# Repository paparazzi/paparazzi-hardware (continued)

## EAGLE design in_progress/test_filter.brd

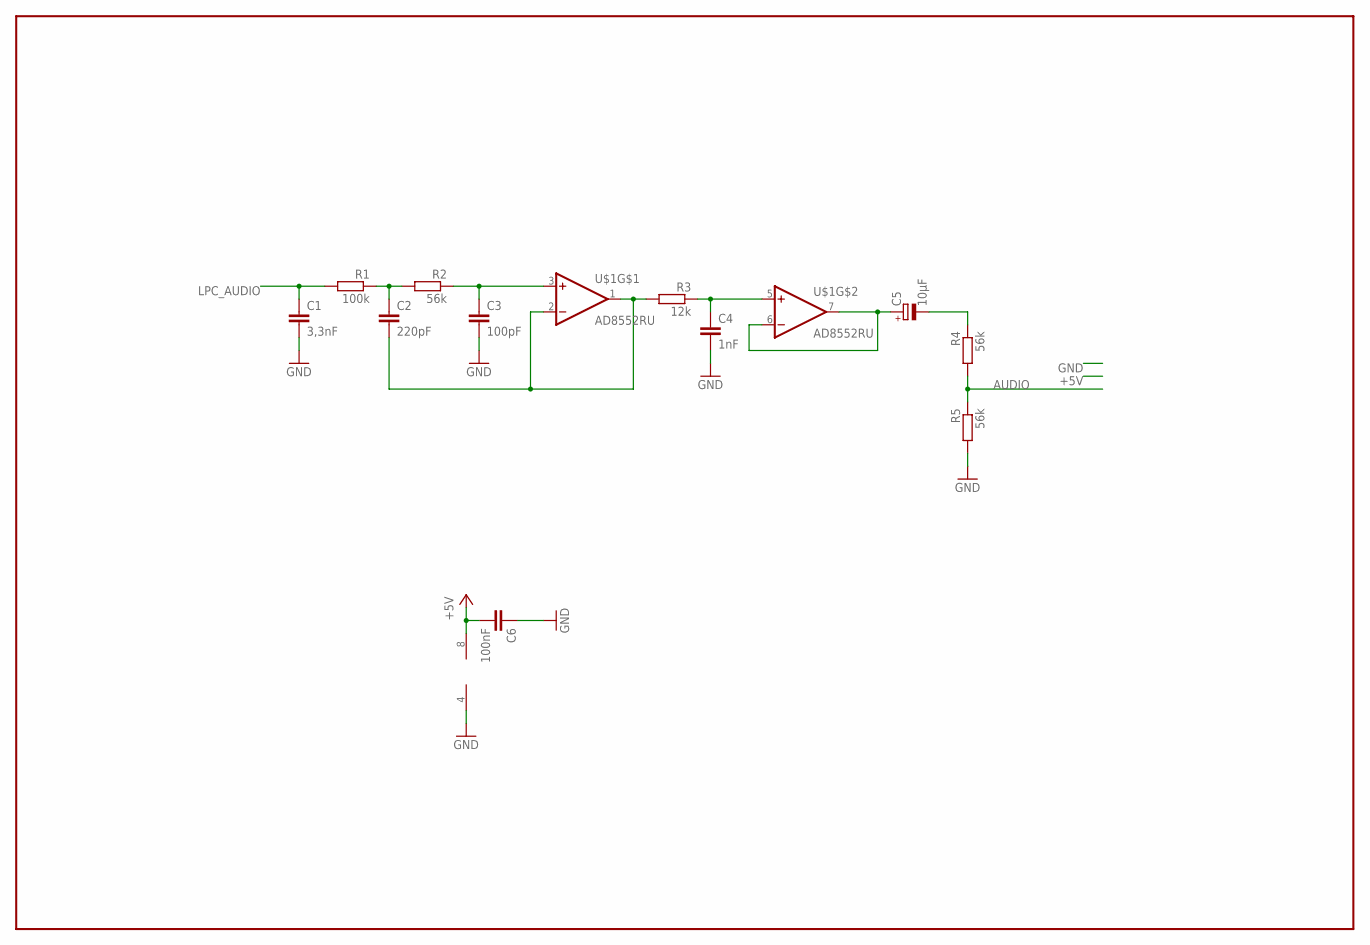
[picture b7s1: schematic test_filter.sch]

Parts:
C1: 3,3nF; C050-030X075
C2: 220pF; C050-030X075
C3: 100pF; C050-030X075
C4: 1nF; C050-030X075
C5: 10µF; E2,5-7
C6: 100nF; C050-030X075
R1: 100k; 0204/7
R2, R4, R5: 56k; 0204/7
R3: 12k; 0204/7
U$1: AD8552RU; TSSOP8

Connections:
+5V: C6.2, U$1.8 (V+)
AUDIO: R4.2, R5.1
GND: C1.2, C3.2, C4.2, C6.1, R5.2, U$1.4 (V-)
LPC_AUDIO: C1.1, R1.2
unnamed: C5.+, U$1.6 (-IN), U$1.7 (OUT)
unnamed: C2.2, R3.2, U$1.1 (OUT), U$1.2 (-IN)
unnamed: C2.1, R1.1, R2.2
unnamed: C3.1, R2.1, U$1.3 (+IN)
unnamed: C5.-, R4.1
unnamed: C4.1, R3.1, U$1.5 (+IN)

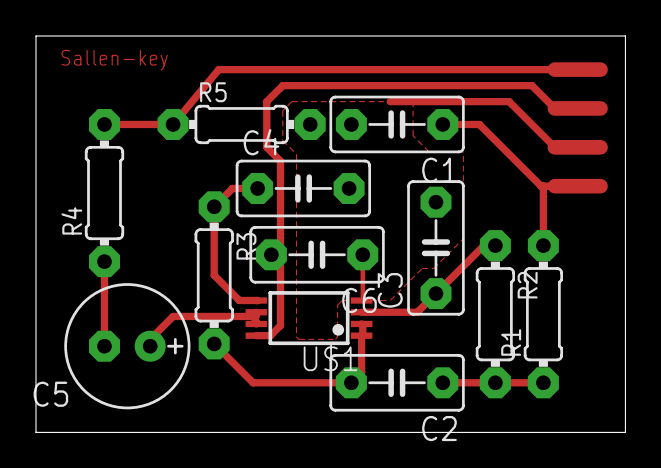
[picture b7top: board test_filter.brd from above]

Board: 2 copper layers, 32.7 x 22.0 mm, 12 parts (0 on the bottom side), 10 nets.

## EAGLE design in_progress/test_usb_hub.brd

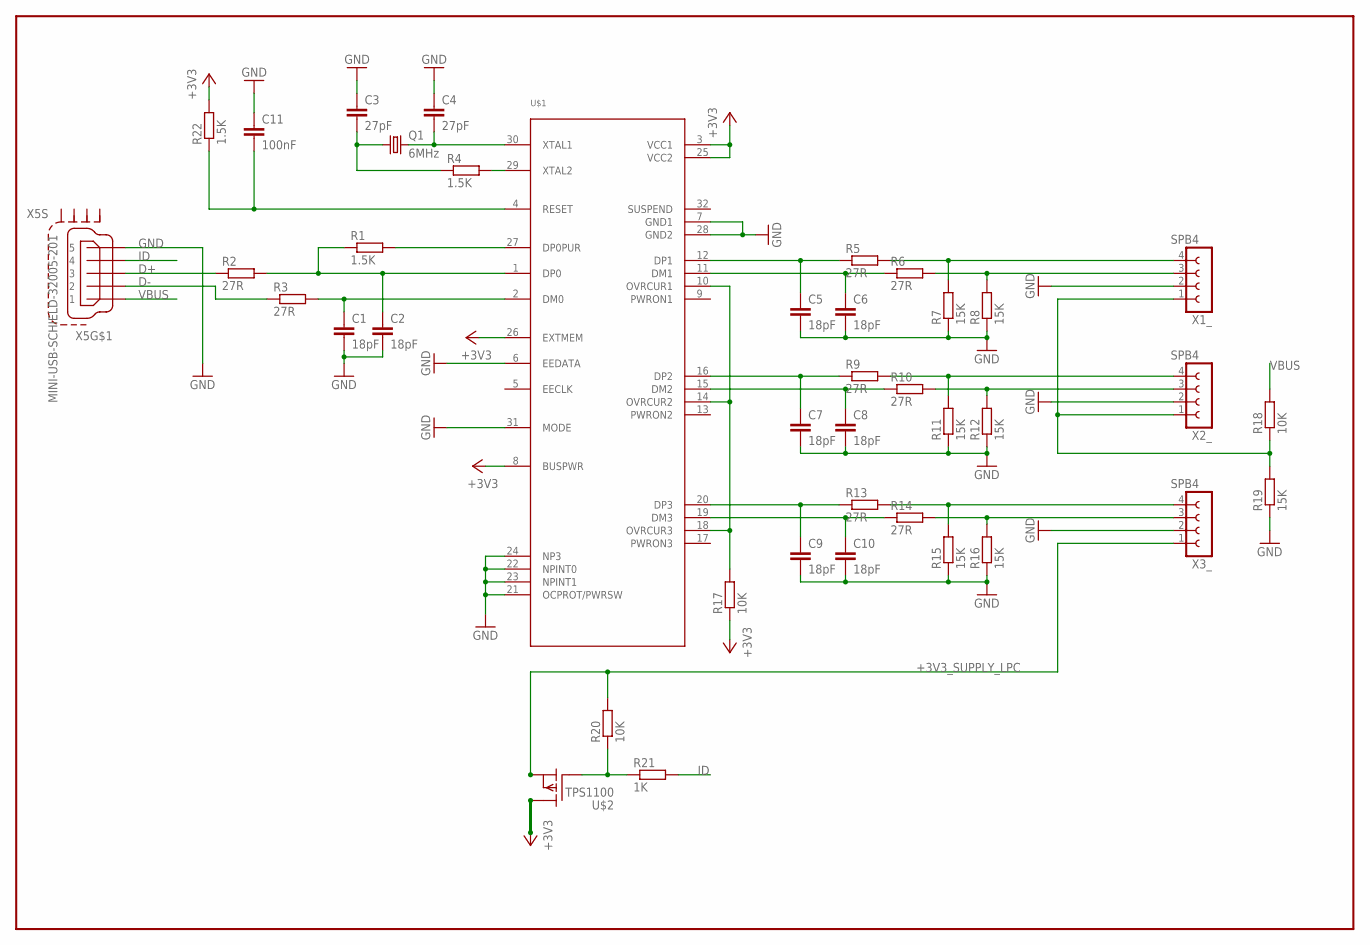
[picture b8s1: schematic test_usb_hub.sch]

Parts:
C1, C2, C5, C6, C7, C8, C9, C10: 18pF; C1206
C3, C4: 27pF; C1206
C11: 100nF; C1206
Q1: 6MHz; HC49U-V
R1, R4, R22: 1.5K; R1206
R2, R3, R5, R6, R9, R10, R13, R14: 27R; R1206
R7, R8, R11, R12, R15, R16, R19: 15K; R1206
R17, R18, R20: 10K; R1206
R21: 1K; R1206
U$1: TUSB2036OK; QFP-32
U$2: TPS1100; SOIC8
X1_, X2_, X3_: SPB4
X5: MINI-USB-SCHIELD-32005-201; 32005-201

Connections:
+3V3: R17.1, R22.2, U$1.3 (VCC1), U$1.8 (BUSPWR), U$1.25 (VCC2), U$1.26 (EXTMEM), U$2.5 (D), U$2.6 (D1), U$2.7 (D2), U$2.8 (D3)
+3V3_SUPPLY_LPC: R20.2, U$2.1 (S), U$2.2 (S1), U$2.3 (S2), X3_.1
D+: R2.1, X5.3
D-: R3.1, X5.2
GND: C1.2, C2.2, C3.1, C4.1, C5.2, C6.2, C7.2, C8.2, C9.2, C10.2, C11.1, R7.1, R8.1, R11.1, R12.1, R15.1, R16.1, R19.1, U$1.6 (EEDATA), U$1.7 (GND1), U$1.21 (OCPROT/PWRSW), U$1.22 (NPINT0), U$1.23 (NPINT1), U$1.24 (NP3), U$1.28 (GND2), U$1.31 (MODE), X1_.2, X2_.2, X3_.2, X5.5
ID: R21.2, X5.4
unnamed: C2.1, R1.1, R2.2, U$1.1 (DP0)
unnamed: C1.1, R3.2, U$1.2 (DM0)
unnamed: R1.2, U$1.27 (DP0PUR)
unnamed: R20.1, R21.1, U$2.4 (G)
unnamed: C4.2, Q1.2, U$1.30 (XTAL1)
unnamed: R4.2, U$1.29 (XTAL2)
unnamed: C3.2, Q1.1, R4.1
unnamed: C5.1, R5.1, U$1.12 (DP1)
unnamed: R5.2, R7.2, X1_.4
unnamed: R6.2, R8.2, X1_.3
unnamed: C6.1, R6.1, U$1.11 (DM1)
unnamed: C7.1, R9.1, U$1.16 (DP2)
unnamed: R9.2, R11.2, X2_.4
unnamed: R10.2, R12.2, X2_.3
unnamed: C8.1, R10.1, U$1.15 (DM2)
unnamed: C9.1, R13.1, U$1.20 (DP3)
unnamed: R13.2, R15.2, X3_.4
unnamed: R14.2, R16.2, X3_.3
unnamed: C10.1, R14.1, U$1.19 (DM3)
unnamed: R17.2, U$1.10 (OVRCUR1), U$1.14 (OVRCUR2), U$1.18 (OVRCUR3)
unnamed: R18.1, R19.2, X1_.1, X2_.1
unnamed: C11.2, R22.1, U$1.4 (RESET)
VBUS: R18.2, X5.1

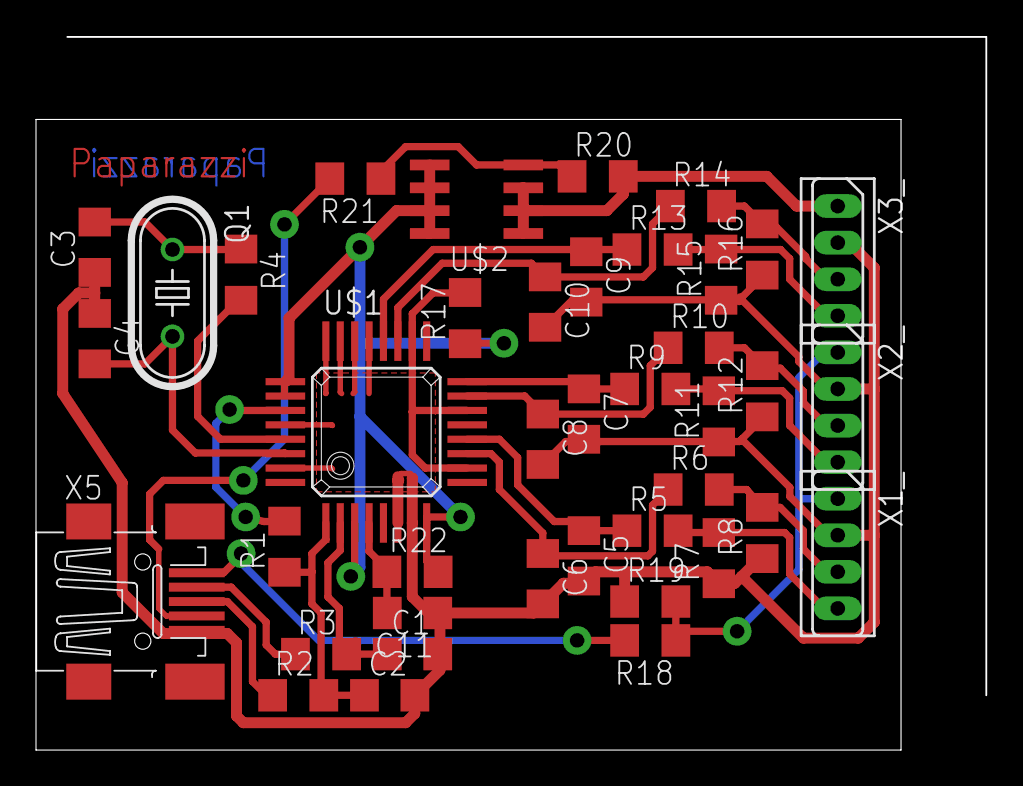
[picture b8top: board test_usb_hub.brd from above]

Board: 2 copper layers, 48.1 x 35.0 mm, 40 parts (0 on the bottom side), 29 nets.
